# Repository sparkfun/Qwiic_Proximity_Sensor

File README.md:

SparkFun VCNL4040 Proximity Sensor (Qwiic) - VCNL4040
===========================================================

[*SparkFun Proximity Sensor Breakout - 20cm, VCNL4040 (Qwiic) (SEN-15177)*](https://www.sparkfun.com/products/15177)

The VCNL4040 is a simple IR presence and ambient light sensor. This sensor is excellent for detecting if something has appeared in front of the sensor. We often see this type of sensor on automatic towel dispensers, automatic faucets, etc. You can detect objects qualitatively up to 20cm away. This means you can detect if something is there, and if it is closer or further away since the last reading, but it's difficult to say it is 7.2cm away. If you need quantitative distance readings (for example sensing that an object is 177mm away) check out the SparkFun Time of Flight (ToF) sensors with mm accuracy.

SparkFun labored with love to create this code. Feel like supporting open source hardware? 
Buy a [breakout board](https://www.sparkfun.com/products/14688) from SparkFun!

Repository Contents
-------------------

* **/Documents** - Datasheets
* **/Hardware** - Eagle design files (.brd, .sch)

Library and Hookup Guide
--------------
* **[Arduino Library](https://github.com/sparkfun/SparkFun_VCNL4040_Arduino_Library)** - Library for reading proximity, ambient light, and IR values.
* **[Hookup Guide](https://learn.sparkfun.com/tutorials/qwiic-proximity-sensor-vcnl4040-hookup-guide)** - Hookup guide for getting started with the SparkFun VCNL4040 Proximity Sensor.

License Information
-------------------

This product is _**open source**_! 

If you have any questions or concerns on licensing, please contact techsupport@sparkfun.com.

Please use, reuse, and modify these files as you see fit. Please maintain attribution to SparkFun Electronics and release any derivative under the same license.

Distributed as-is; no warranty is given.

- Your friends at SparkFun.

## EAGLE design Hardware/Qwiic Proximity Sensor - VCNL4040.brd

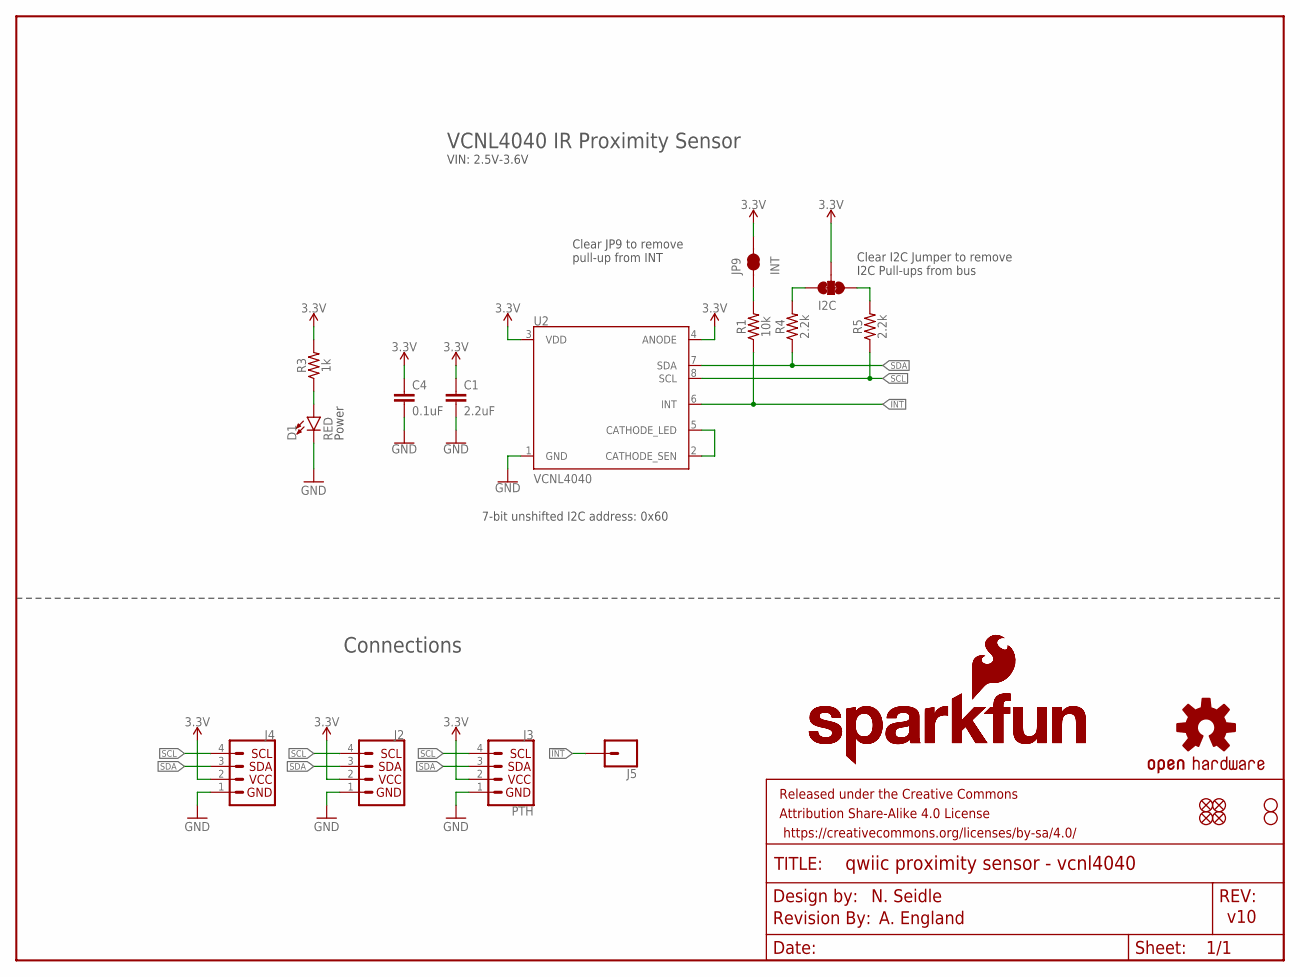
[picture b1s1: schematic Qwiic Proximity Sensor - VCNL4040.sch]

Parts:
C1: 2.2uF; 0603
C4: 0.1uF; 0603
D1: RED; LED-0603
FRAME1: FRAME-LETTER; CREATIVE_COMMONS
I2C: JUMPER-SMT_3_2-NC_TRACE_SILK; SMT-JUMPER_3_2-NC_TRACE_SILK
J2, J4: QWIIC_CONNECTORJS-1MM; 1X04_1MM_RA
J3: PTH; 1X04_NO_SILK
J5: CONN_01PTH_NO_SILK_YES_STOP; 1X01_NO_SILK
JP1, JP2, JP5, JP6: FIDUCIALUFIDUCIAL; MICRO-FIDUCIAL
JP3, JP4: STAND-OFF
JP9: INT; PAD-JUMPER-2-NC_BY_TRACE_YES_SILK
LOGO1: OSHW-LOGOMINI; OSHW-LOGO-MINI
LOGO2: REVISION
R1: 10k; 0603
R3: 1k; 0603
R4, R5: 2.2k; 0603
U2: VCNL4040; SPARKX_VCNL4040
U$1, U$2: SFE_LOGO_NAME_FLAME.1_INCH; SFE_LOGO_NAME_FLAME_.1

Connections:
3.3V: C1.1, C4.1, I2C.2, J2.2, J3.2 (VCC), J4.2, JP9.2, R3.2, U2.3 (VDD), U2.4 (ANODE)
!INT: J5.1, R1.1, U2.6 (INT)
GND: C1.2, C4.2, D1.C, J2.1, J3.1 (GND), J4.1, U2.1 (GND)
unnamed: I2C.1, R5.2
unnamed: I2C.3, R4.2
unnamed: D1.A, R3.1
unnamed: JP9.1, R1.2
unnamed: U2.2 (CATHODE_SEN), U2.5 (CATHODE_LED)
SCL: J2.4, J3.4 (SCL), J4.4, R5.1, U2.8 (SCL)
SDA: J2.3, J3.3 (SDA), J4.3, R4.1, U2.7 (SDA)

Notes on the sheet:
N. Seidle
v10
7-bit unshifted I2C address: 0x60
Clear I2C Jumper to remove I2C Pull-ups from bus
Clear JP9 to remove pull-up from INT
Power
VCNL4040 IR Proximity Sensor
Connections
A. England
VIN: 2.5V-3.6V

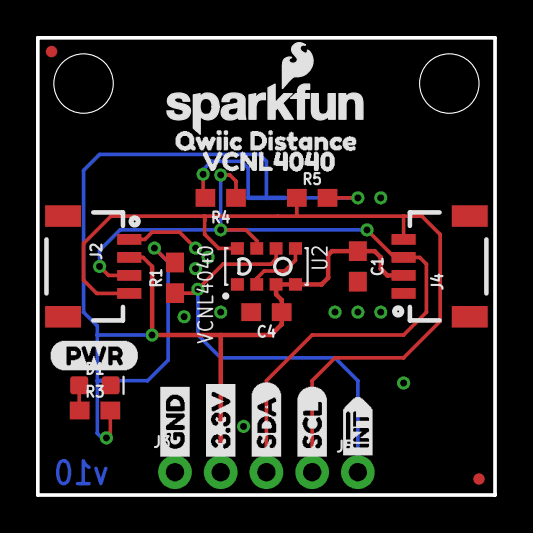
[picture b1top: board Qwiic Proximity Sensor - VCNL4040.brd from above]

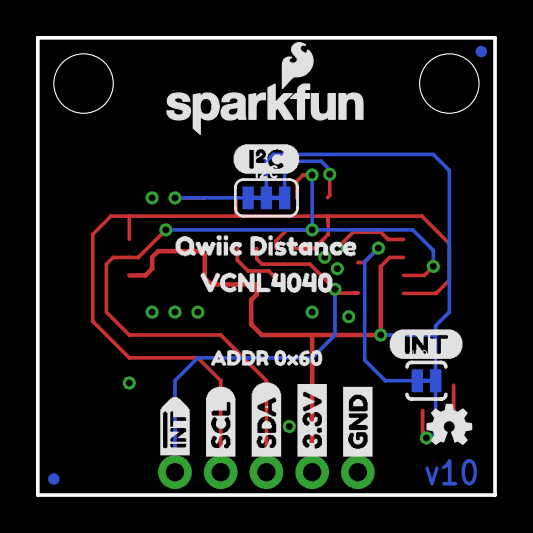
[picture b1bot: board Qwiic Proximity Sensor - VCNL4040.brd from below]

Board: 2 copper layers, 25.4 x 25.4 mm, 43 parts (16 on the bottom side), 10 nets.

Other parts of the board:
U$3, U$22: GND1
U$4, U$21: 3#3V2
U$5, U$27: SDA8
U$6, U$26: SCL9
U$7, U$25: #INT14
U$8: ADDR_0X600
U$10: (PWR)
U$11: (I_SUPER2_C)
U$12: (INT)
U$13, U$14: VCNL40401
U$15, U$19: QWIIC_DISTANCE0

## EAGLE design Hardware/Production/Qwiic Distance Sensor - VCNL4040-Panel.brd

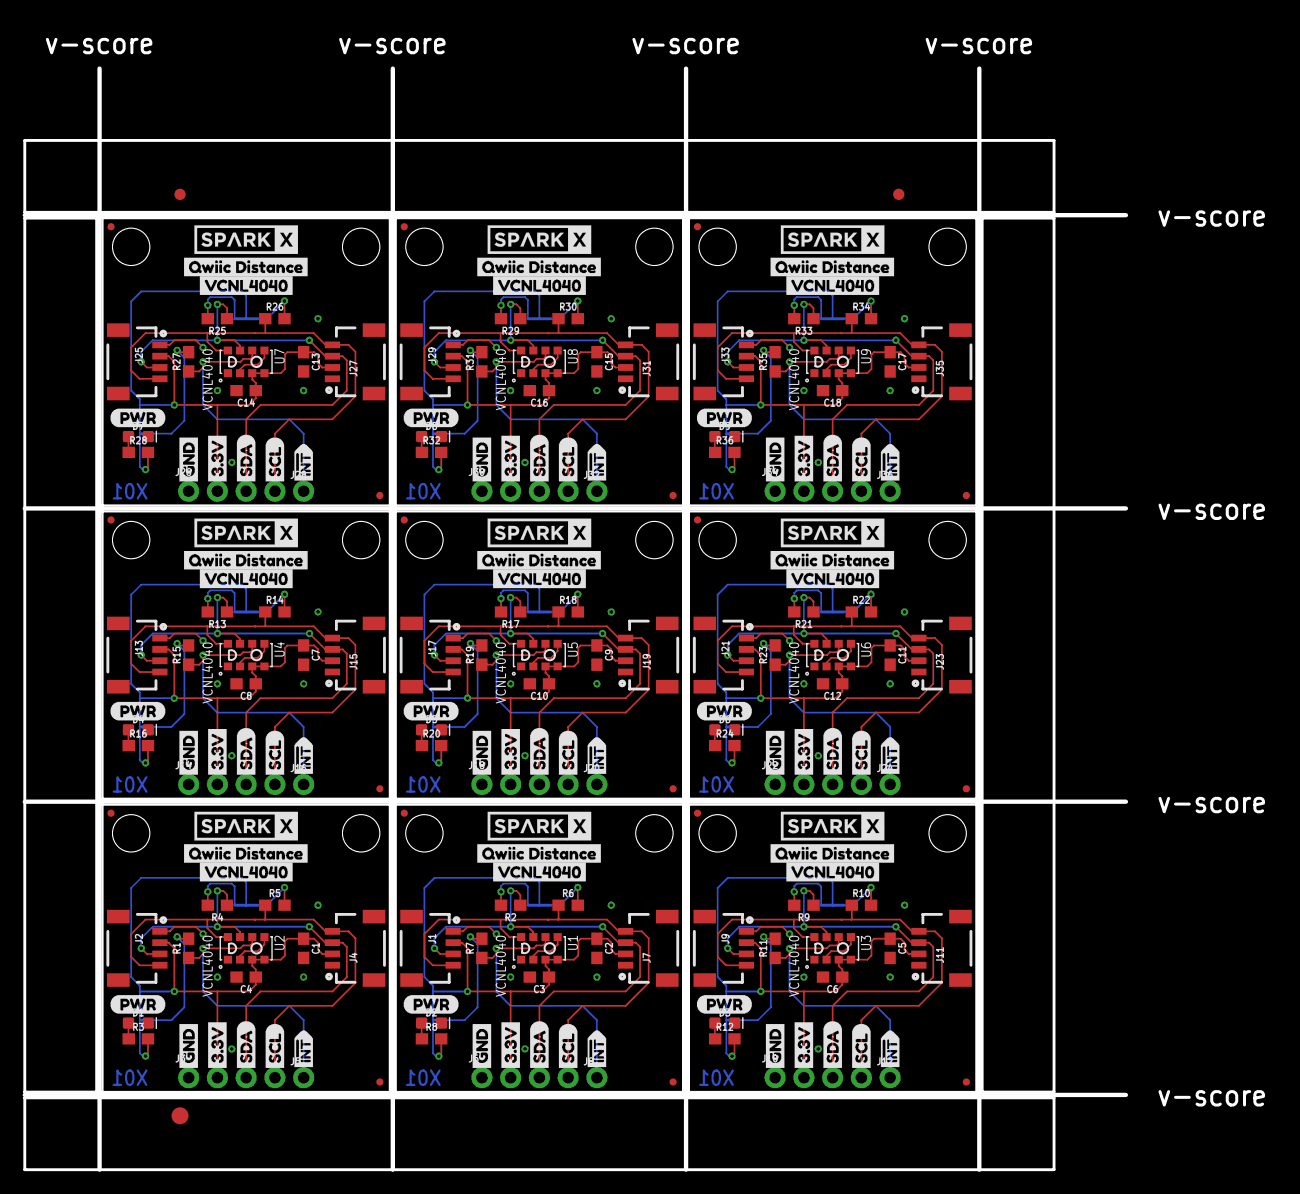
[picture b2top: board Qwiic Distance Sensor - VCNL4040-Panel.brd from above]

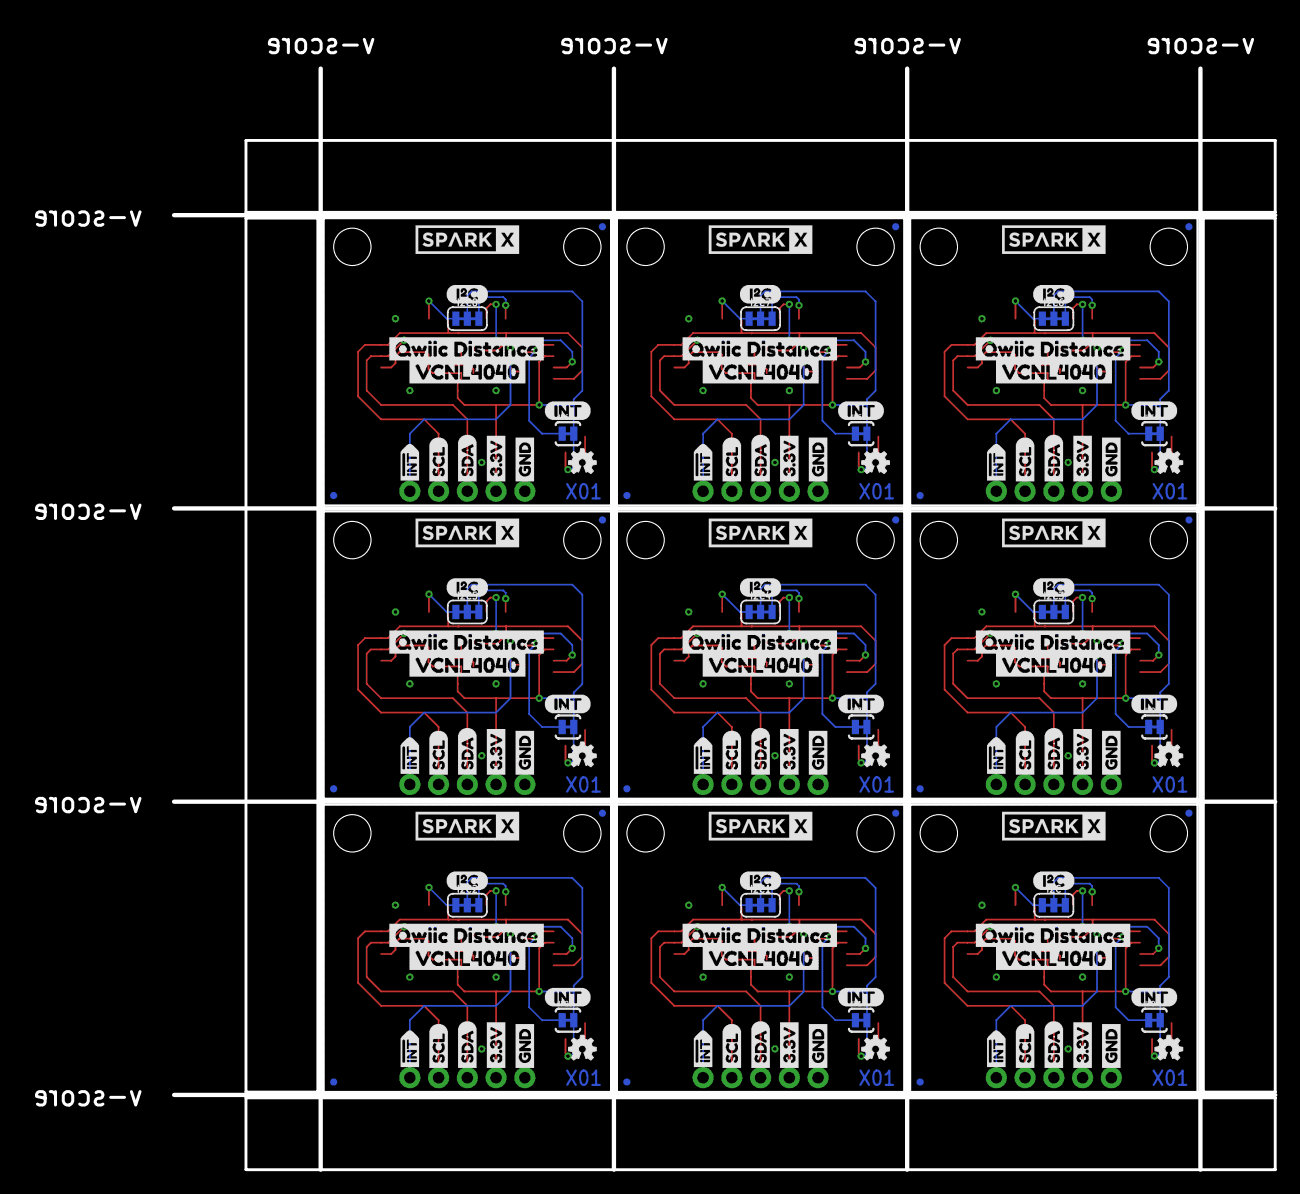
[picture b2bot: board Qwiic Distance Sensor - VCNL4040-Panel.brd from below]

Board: 2 copper layers, 97.3 x 97.3 mm, 363 parts (135 on the bottom side), 90 nets.

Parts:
C1, C2, C5, C7, C9, C11, C13, C15, C17: 2.2uF; 0603
C3, C4, C6, C8, C10, C12, C14, C16, C18: 0.1uF; 0603
D1, D2, D3, D4, D5, D6, D7, D8, D9: RED; LED-0603
E$1, E$2: FIDUCIAL-1X2
E$3: FIDUCIAL-1.5X3
I2C, I2C1, I2C2, I2C3, I2C4, I2C5, I2C6, I2C7, I2C8: SMT-JUMPER_3_2-NC_TRACE_SILK
J1, J2, J4, J7, J9, J11, J13, J15, J17, J19, J21, J23, J25, J27, J29, J31, J33, J35: SMD; 1X04_1MM_RA
J3, J6, J10, J14, J18, J22, J26, J30, J34: PTH; 1X04_NO_SILK
J5, J8, J12, J16, J20, J24, J28, J32, J36: 1X01_NO_SILK
JP1, JP2, JP5, JP6, JP10, JP11, JP12, JP13, JP17, JP18, JP19, JP20, JP24, JP25, JP26, JP27, JP31, JP32, JP33, JP34, JP38, JP39, JP40, JP41, JP45, JP46, JP47, JP48, JP52, JP53, JP54, JP55, JP59, JP60, JP61, JP62: FIDUCIALUFIDUCIAL; MICRO-FIDUCIAL
JP3, JP4, JP7, JP8, JP15, JP16, JP22, JP23, JP29, JP30, JP36, JP37, JP43, JP44, JP50, JP51, JP57, JP58: STAND-OFF
JP9, JP14, JP21, JP28, JP35, JP42, JP49, JP56, JP63: INT; PAD-JUMPER-2-NC_BY_TRACE_YES_SILK
LOGO1, LOGO2, LOGO3, LOGO4, LOGO5, LOGO6, LOGO7, LOGO8, LOGO9: OSHW-LOGOMINI; OSHW-LOGO-MINI
R1, R7, R11, R15, R19, R23, R27, R31, R35: 10k; 0603
R2, R4, R5, R6, R9, R10, R13, R14, R17, R18, R21, R22, R25, R26, R29, R30, R33, R34: 2.2k; 0603
R3, R8, R12, R16, R20, R24, R28, R32, R36: 1k; 0603
U1, U2, U3, U4, U5, U6, U7, U8, U9: VCNL4040
U$1, U$2, U$8, U$9, U$39, U$40, U$58, U$59, U$77, U$78, U$96, U$97, U$115, U$116, U$134, U$135, U$153, U$154: SPARKX-LOGO4; SPARKX-MEDIUM
U$3, U$20, U$22, U$29, U$44, U$48, U$63, U$67, U$82, U$86, U$101, U$105, U$120, U$124, U$139, U$143, U$158, U$162: GND1
U$4, U$18, U$21, U$30, U$43, U$49, U$62, U$68, U$81, U$87, U$100, U$106, U$119, U$125, U$138, U$144, U$157, U$163: 3#3V2
U$5, U$27, U$28, U$31, U$47, U$50, U$66, U$69, U$85, U$88, U$104, U$107, U$123, U$126, U$142, U$145, U$161, U$164: SDA8
U$6, U$24, U$26, U$32, U$46, U$51, U$65, U$70, U$84, U$89, U$103, U$108, U$122, U$127, U$141, U$146, U$160, U$165: SCL9
U$7, U$23, U$25, U$33, U$45, U$52, U$64, U$71, U$83, U$90, U$102, U$109, U$121, U$128, U$140, U$147, U$159, U$166: #INT14
U$10, U$34, U$53, U$72, U$91, U$110, U$129, U$148, U$167: (PWR)
U$11, U$35, U$54, U$73, U$92, U$111, U$130, U$149, U$168: (I_SUPER2_C)
U$12, U$36, U$55, U$74, U$93, U$112, U$131, U$150, U$169: (INT)
U$13, U$37, U$56, U$75, U$94, U$113, U$132, U$151, U$170: VCNL40400
U$14, U$38, U$57, U$76, U$95, U$114, U$133, U$152, U$171: VCNL40401
U$15, U$16, U$41, U$60, U$79, U$98, U$117, U$136, U$155: QWIIC_DISTANCE7
U$17, U$19, U$42, U$61, U$80, U$99, U$118, U$137, U$156: QWIIC_DISTANCE9

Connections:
3.3V: C1.1, C4.1, I2C.2, J2.2, J3.2, J4.2, JP9.2, R3.2, U2.3, U2.4
3.3V1: C2.1, C3.1, I2C1.2, J1.2, J6.2, J7.2, JP14.2, R8.2, U1.3, U1.4
3.3V2: C5.1, C6.1, I2C2.2, J9.2, J10.2, J11.2, JP21.2, R12.2, U3.3, U3.4
3.3V3: C7.1, C8.1, I2C3.2, J13.2, J14.2, J15.2, JP28.2, R16.2, U4.3, U4.4
3.3V4: C9.1, C10.1, I2C4.2, J17.2, J18.2, J19.2, JP35.2, R20.2, U5.3, U5.4
3.3V5: C11.1, C12.1, I2C5.2, J21.2, J22.2, J23.2, JP42.2, R24.2, U6.3, U6.4
3.3V6: C13.1, C14.1, I2C6.2, J25.2, J26.2, J27.2, JP49.2, R28.2, U7.3, U7.4
3.3V7: C15.1, C16.1, I2C7.2, J29.2, J30.2, J31.2, JP56.2, R32.2, U8.3, U8.4
3.3V8: C17.1, C18.1, I2C8.2, J33.2, J34.2, J35.2, JP63.2, R36.2, U9.3, U9.4
!INT: J5.1, R1.1, U2.6
!INT1: J8.1, R7.1, U1.6
!INT2: J12.1, R11.1, U3.6
!INT3: J16.1, R15.1, U4.6
!INT4: J20.1, R19.1, U5.6
!INT5: J24.1, R23.1, U6.6
!INT6: J28.1, R27.1, U7.6
!INT7: J32.1, R31.1, U8.6
!INT8: J36.1, R35.1, U9.6
GND: C1.2, C4.2, D1.C, J2.1, J3.1, J4.1, U2.1
GND1: C2.2, C3.2, D2.C, J1.1, J6.1, J7.1, U1.1
GND2: C5.2, C6.2, D3.C, J9.1, J10.1, J11.1, U3.1
GND3: C7.2, C8.2, D4.C, J13.1, J14.1, J15.1, U4.1
GND4: C9.2, C10.2, D5.C, J17.1, J18.1, J19.1, U5.1
GND5: C11.2, C12.2, D6.C, J21.1, J22.1, J23.1, U6.1
GND6: C13.2, C14.2, D7.C, J25.1, J26.1, J27.1, U7.1
GND7: C15.2, C16.2, D8.C, J29.1, J30.1, J31.1, U8.1
GND8: C17.2, C18.2, D9.C, J33.1, J34.1, J35.1, U9.1
unnamed: I2C.1, R5.2
unnamed: I2C.3, R4.2
unnamed: D1.A, R3.1
unnamed: JP9.1, R1.2
unnamed: I2C1.1, R6.2
unnamed: U2.2, U2.5
unnamed: I2C1.3, R2.2
unnamed: JP14.1, R7.2
unnamed: D2.A, R8.1
unnamed: U1.2, U1.5
unnamed: I2C2.1, R10.2
unnamed: I2C2.3, R9.2
unnamed: JP21.1, R11.2
unnamed: D3.A, R12.1
unnamed: U3.2, U3.5
unnamed: I2C3.1, R14.2
unnamed: I2C3.3, R13.2
unnamed: JP28.1, R15.2
unnamed: D4.A, R16.1
unnamed: U4.2, U4.5
unnamed: I2C4.1, R18.2
unnamed: I2C4.3, R17.2
unnamed: JP35.1, R19.2
unnamed: D5.A, R20.1
unnamed: U5.2, U5.5
unnamed: I2C5.1, R22.2
unnamed: I2C5.3, R21.2
unnamed: JP42.1, R23.2
unnamed: D6.A, R24.1
unnamed: U6.2, U6.5
unnamed: I2C6.1, R26.2
unnamed: I2C6.3, R25.2
unnamed: JP49.1, R27.2
unnamed: D7.A, R28.1
unnamed: U7.2, U7.5
unnamed: I2C7.1, R30.2
unnamed: I2C7.3, R29.2
unnamed: JP56.1, R31.2
unnamed: D8.A, R32.1
unnamed: U8.2, U8.5
unnamed: I2C8.1, R34.2
unnamed: I2C8.3, R33.2
unnamed: JP63.1, R35.2
unnamed: D9.A, R36.1
unnamed: U9.2, U9.5
SCL: J2.4, J3.4, J4.4, R5.1, U2.8
SCL1: J1.4, J6.4, J7.4, R6.1, U1.8
SCL2: J9.4, J10.4, J11.4, R10.1, U3.8
SCL3: J13.4, J14.4, J15.4, R14.1, U4.8
SCL4: J17.4, J18.4, J19.4, R18.1, U5.8
SCL5: J21.4, J22.4, J23.4, R22.1, U6.8
SCL6: J25.4, J26.4, J27.4, R26.1, U7.8
SCL7: J29.4, J30.4, J31.4, R30.1, U8.8
SCL8: J33.4, J34.4, J35.4, R34.1, U9.8
SDA: J2.3, J3.3, J4.3, R4.1, U2.7
SDA1: J1.3, J6.3, J7.3, R2.1, U1.7
SDA2: J9.3, J10.3, J11.3, R9.1, U3.7
SDA3: J13.3, J14.3, J15.3, R13.1, U4.7
SDA4: J17.3, J18.3, J19.3, R17.1, U5.7
SDA5: J21.3, J22.3, J23.3, R21.1, U6.7
SDA6: J25.3, J26.3, J27.3, R25.1, U7.7
SDA7: J29.3, J30.3, J31.3, R29.1, U8.7
SDA8: J33.3, J34.3, J35.3, R33.1, U9.7

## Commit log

2019-01-25 post checklist changes
2019-02-22 Updated library repository link and description
2019-02-28 Update README.md
    Update new product link and hookup guide content.

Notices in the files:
parts and their libraries:
SparkFun-Resistors: Licensing: Creative Commons ShareAlike 4.0 International - https://creativecommons.org/licenses/by-sa/4.0
SparkFun-Aesthetics: Released under the Creative Commons Attribution Share-Alike 4.0 License
SparkFun-Aesthetics: https://creativecommons.org/licenses/by-sa/4.0
